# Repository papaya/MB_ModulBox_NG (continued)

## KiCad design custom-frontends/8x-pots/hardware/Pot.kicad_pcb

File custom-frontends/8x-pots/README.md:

# 8x-pots — Module custom 8 potentiomètres rotatifs (AIN)

## Description

Module potentiomètres rotatifs (8 canaux) pour le contrôle de paramètres continus MIDI (volume, filtre, effets, etc.). Chaque potentiomètre est lu sur une voie analogique indépendante. La carte ne contient **aucun convertisseur analogique-numérique** : elle expose 8 curseurs sur un connecteur IDC, reliés au module **AINSER64** (MCP3208 + CD4051) du bus AIN.

## Spécifications techniques

- 8 potentiomètres rotatifs (10 kΩ), empreinte `RK09L and RK09D`
- **Tension de référence : +3V0** (et non +5V) — la borne `+3V0` alimente les deux extrémités de chaque potentiomètre
- Sortie : 8 curseurs + GND + +3V0 sur un connecteur **IDC 2x05 P2.54mm** (`J1`)
- Lecture : via le module **AINSER64** du bus AIN (broche `J19` du Core32F4, SPI)
- Aucune résistance, aucun condensateur, aucun circuit actif sur la carte

## Composants principaux

| Type | Dénomination | Qté |
|------|-------------|-----|
| Potentiomètre rotatif | RK09D1130C1B / RK09L1140A5L (10 kΩ) | 8 |
| Connecteur | IDC Header 2x05 P2.54mm Vertical (`J1`) | 1 |
| Vis de fixation | MountingHole 3.2mm M3 | 6 |

> Il n'y a **pas de LED sur cette carte**
## Brochage / Mapping MIDIbox NG

### Connecteur `J1` — vers module AINSER64 (bus AIN, `J19` du Core)

| Broche | Signal | Description |
|--------|--------|-------------|
| 1 | GND | Masse commune (référence 0 V) |
| 2 | +3V0 | Alimentation des potentiomètres (borne haute) |
| 3 | `J1-A0` | Curseur du potentiomètre **pot2** |
| 4 | `J1-A1` | Curseur du potentiomètre **pot1** |
| 5 | `J1-A2` | Curseur du potentiomètre **pot3** |
| 6 | `J1-A3` | Curseur du potentiomètre **pot6** |
| 7 | `J1-A4` | Curseur du potentiomètre **pot4** |
| 8 | `J1-A5` | Curseur du potentiomètre **pot7** |
| 9 | `J1-A6` | Curseur du potentiomètre **pot5** |
| 10 | `J1-A7` | Curseur du potentiomètre **pot8** |

> **Câblage du potentiomètre (vérifié dans le schéma KiCad)** : patte 1 → GND, patte 2 → **curseur** (→ broche `J1` correspondante), patte 3 → **+3V0**.

> Le curseur étant relié à l'entrée analogique de l'AINSER64, la plage de mesure est **0 .. 3,0 V** (et non 0 .. 5 V). L'AINSER64 (ADC MCP3208 12 bits) mesure donc 0..3 V avec une résolution effective d'environ 10 bits.

> **Les entrées analogiques non utilisées de l'AINSER64 doivent être reliées à la masse**, sinon l'application émet des valeurs aléatoires.

### Module AINSER64 (rappel)

- Connecteur : **`J19`** du Core STM32F4 (SPI, 2 chip-selects `RC1`/`RC2`)
- Architecture : 1 × **MCP3208** (ADC 12 bits) + 8 × **CD4051** (multiplexeurs 8:1) + 1 × 74HC595
- Capacité : 64 entrées par module, jusqu'à 2 modules (128 voies) supportés par MIDIbox NG
- Les 8 entrées de chaque connecteur `J6`..`J13` de l'AINSER64 disposent de **+5V et GND** dédiés ; si la tension de référence de 3,0 V est souhaitée, alimenter les potentiomètres séparément (c'est le cas ici : +3V0 local à la carte)

## Variante `Pot-X2` (montage 4x2)

- `hardware/Pot-X2.kicad_pcb` : variante **2 plaques de 4 potentiomètres** empilées (41 empreintes)
- ⚠️ **Cette variante n'a pas de schéma KiCad associé** et contient des empreintes non annotées (`REF**`) ainsi que 10 pads non connectés : elle est fournie **pour référence**, à vérifier avant fabrication
- Le schéma `Pot.kicad_sch` correspond à la variante **verticale** (8 potentiomètres sur une plaque)

## Notes de montage et astuces DIY

- Vérifier le câblage du curseur vers la broche `J1` avant mise sous tension
- Les potentiomètres sont sur la carte verticale ; l'empilement 4x2 (`Pot-X2`) est mécaniquement séparé
- Fichiers 3D : Potars_V4.wrl (boîtier), Potars_eurorack.step (montage Eurorack)

## Documentation de fabrication

- `hardware/` : sources KiCad (`Pot.kicad_pro`, `Pot.kicad_sch`, `Pot.kicad_pcb`, + variante `Pot-X2.kicad_pcb`)
- `hardware/3D/` : modèles 3D des potentiomètres (`.wrl`, `.step`)
- `production/` : Gerbers, BOM (Pot.csv), netlist (`.xml`), archives de fabrication
- Blog : [4X2-POTS-v0.2 sur ksir-diy.blogspot.com](https://ksir-diy.blogspot.com/)
## Assets de visualisation

| Type | Fichier | Description |
|------|---------|-------------|
| Top view | `3d-top.png` | Vue de dessus du PCB |
| Iso 3D | `3d-iso.png` | Vue isométrique avec composants |
| Pot 4x2 | `pot4x2.png` | Vue du montage 4x2 pots |
| Screenshot | `Screenshot%202023-05-19%20153745.png` | Capture d'écran du design |

---

## Conception & Compatibilité

Carte d'interface **originale MB MODULBOX NG** (conception Ksir), compatible avec les bus et modules du système MIDIbox NG. Ce n'est **pas** un module officiel MIDIbox.

> **Origine et usage :** conception originale MB MODULBOX NG, prévue pour le DIY/personnel. Aucune licence formelle n'est publiée dans le dépôt ; voir le README racine. **Aucune garantie ni engagement** n'est fourni sur la justesse du câblage ou du routage.

> ⚠️ **Avertissement :** documentation de passion, **non professionnelle**. Fournie **sans garantie ni engagement**, **sans support technique**. Des **erreurs sont possibles** (schémas, valeurs, câblage). À vos risques et périls : vérifiez tout avant de fabriquer et de mettre sous tension.

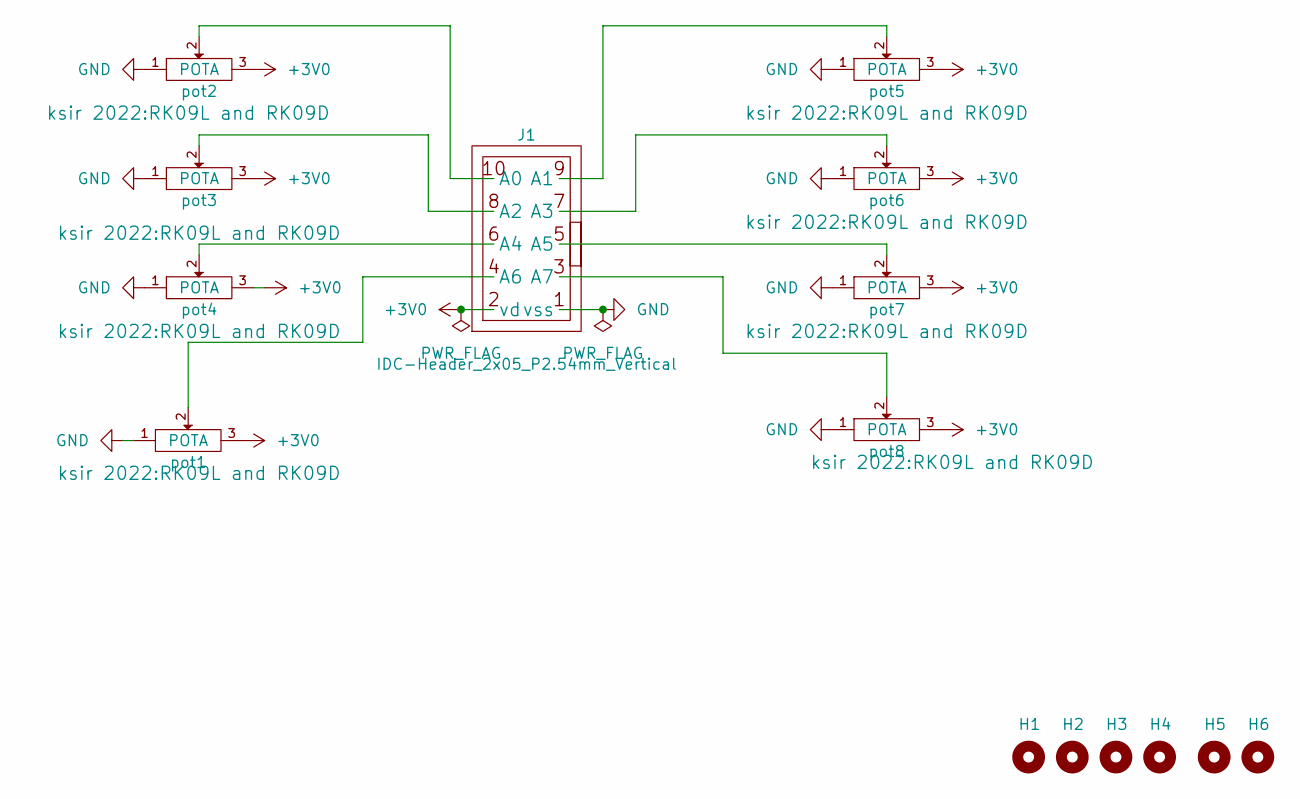
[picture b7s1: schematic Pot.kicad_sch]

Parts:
H1, H2, H3, H4, H5, H6: MountingHole; MountingHole_3.2mm_M3
J1: IDC-Header_2x05_P2.54mm_Vertical
pot1, pot2, pot3, pot4, pot5, pot6, pot7, pot8: POTA; RK09L and RK09D

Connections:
+3V0: J1.2 (vd), pot1.3 (vd), pot2.3 (vd), pot3.3 (vd), pot4.3 (vd), pot5.3 (vd), pot6.3 (vd), pot7.3 (vd), pot8.3 (vd)
GND: J1.1 (vss), pot1.1 (vss_masse), pot2.1 (vss_masse), pot3.1 (vss_masse), pot4.1 (vss_masse), pot5.1 (vss_masse), pot6.1 (vss_masse), pot7.1 (vss_masse), pot8.1 (vss_masse)
unnamed: J1.10 (A0), pot2.2
unnamed: J1.9 (A1), pot5.2
unnamed: J1.8 (A2), pot3.2
unnamed: J1.7 (A3), pot6.2
unnamed: J1.6 (A4), pot4.2
unnamed: J1.5 (A5), pot7.2
unnamed: J1.4 (A6), pot1.2
unnamed: J1.3 (A7), pot8.2

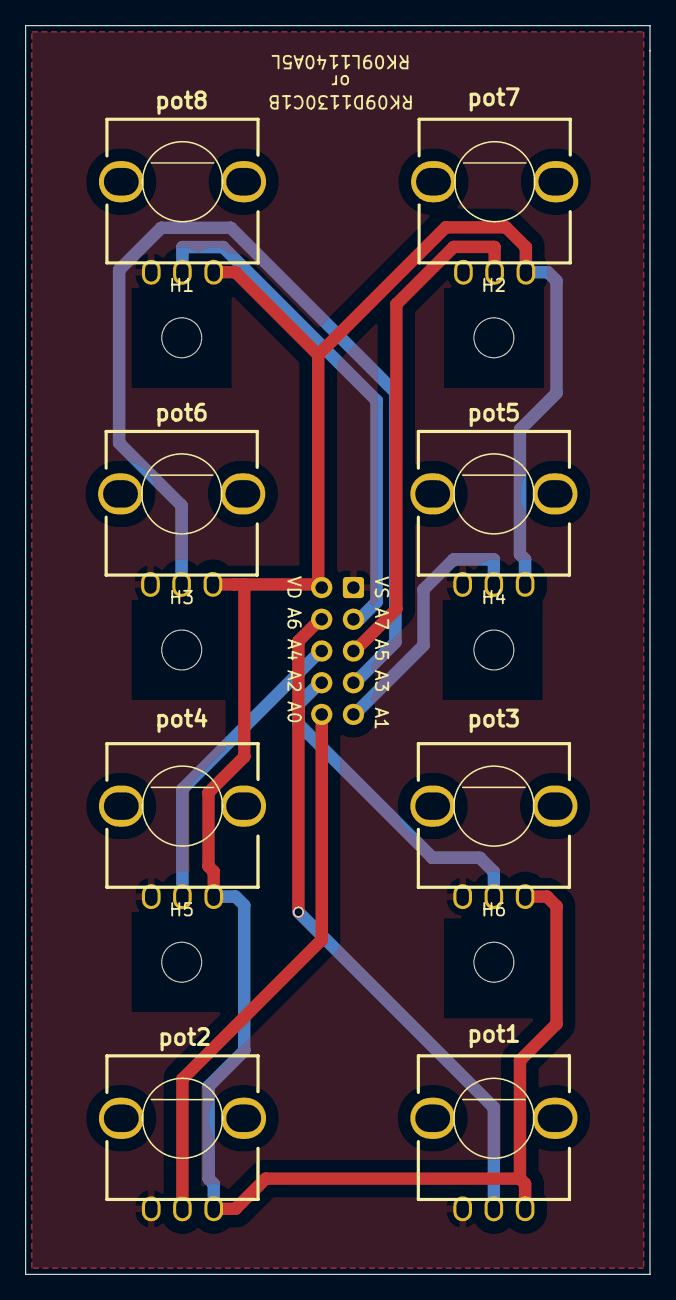
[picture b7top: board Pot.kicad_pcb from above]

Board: 2 copper layers, 50.0 x 100.0 mm, 15 parts (1 on the bottom side), 10 nets.

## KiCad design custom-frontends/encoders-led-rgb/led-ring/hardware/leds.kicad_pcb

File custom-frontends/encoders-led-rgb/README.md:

# encoders-led-rgb — Carte 8 encodeurs PEC16 + 128 LED WS2812 (DIN + WS2812)

## Description
Carte de front-end integrant **8 encodeurs rotatifs avec poussoir** (PEC16) et **128 LED RGB adressables WS2812** (anneaux lumineux). Chaque encodeur genere des evenements MIDI via le **bus DIN**, et l'eclairage est commande par **une ligne de donnees WS2812**, les 128 LED etant **cascadees en serie**.
Se compose de 3 PCB;
un pcb avec les leds
un pcb avec les encodeurs
un pcb pour les connecteurs
un front panel en aluminium 
des diffuseur de lumiere translucide imprimé en 3d
des masque de lumiere imprimé en 3d noir pour empecher la lumiére de se diffuser ailleur  
📖 **Article de référence :** [4X2 ENC-SW-16-LED-RING-RGB (PEC16)](https://ksir-diy.blogspot.com/) sur le blog Ksir DIY'S — modèles PEC16 fonctionne, déja testé!

> ⚠️ Attention a la consomation des leds , j'ai baissé la luminosité a entre 5 et 10 % pour garder une consomation limité (entre 0,5 et 1 A sur la consomation totale du controleur)
> ⚠️ **Les LED WS2812 ne se connectent PAS sur le bus DOUT (74HC595).** Elles recoivent une ligne de donnees specifique d'une sortie WS2812 du **Core32F4** (`J4A` / `J4B`). L'alimentation 5V des LED doit etre fournie **separement** (pas via `J4A`/`J4B`).
>
> **Les 128 LED WS2812 sont en cascade** au niveau du cablage physique (chaine de donnees),  **elles sont adressables individuellement**. Il est possible de commander chaque LED a une couleur differente.

## Spécifications techniques
- **8 encodeurs rotatifs avec poussoir integre** — PEC16 (`PEC16-4XXXF-SXXXX`, empreinte `PEC164120FS0012`) : 2 sorties de phase (A, B) + 1 poussoir
- **24 entrees DIN** au total (8 × A, 8 × B, 8 × poussoir), reparties sur 3 connecteurs `J11`, `J12`, `J13`
- **128 × WS2812-2020** (PLCC4 2.0 × 2.0 mm) en **cascade serie** unique : `J4` -> D1 -> D2 -> ... -> D128 -> `J5`
- 128 × condensateur de decoupling 100 nF sur chaque LED
- **Aucune resistance de pull-up sur la carte** : le pull-up 10 kΩ est porte par le module **DIN** (74HC165)
- 2 alimentations distinctes : `+5VA` (analogique, `J44`) et `+5VD` (digitale, `J45`)

## Composants principaux
| Type | Dénomination | Qté |
|------|-------------|-----|
| Encodeur rotatif a poussoir | PEC16 (`PEC164120FS0012`) | 8 |
| LED RGB adressable | WS2812B (`LED_WS2812B-2020_PLCC4_2.0x2.0mm`) | 128 |
| Condensateur | C 100 nF | 128 |
| Connecteur DIN | IDC Header 2x05 (`J11`, `J12`, `J13`) | 3 |
| Connecteur WS2812 | PinSocket 1x03 (`J4` entree, `J5` sortie) | 2 |
| Connecteur alimentation | IDC 2x05 (`J44` = +5VA, `J45` = +5VD) | 2 |
| Connecteurs de report | PinHeader / PinSocket 1x03 et 1x06 (`J14`, `J15`, `J20`-`J25`, `J30`-`J35`) | 18 |

## Brochage / Mapping MIDIbox NG

### `J11` — poussoirs des encodeurs (8 entrees DIN) Se connecte sur carte DIN 
| Broche | Signal | Description |
|--------|--------|-------------|
| 1 | GND | Masse commune |
| 2 | — | Non connectee |
| 3 | `C_SW8` | Poussoir de l'encodeur **8** |
| 4 | `C_SW7` | Poussoir de l'encodeur **7** |
| 5 | `C_SW6` | Poussoir de l'encodeur **6** |
| 6 | `C_SW5` | Poussoir de l'encodeur **5** |
| 7 | `C_SW4` | Poussoir de l'encodeur **4** |
| 8 | `C_SW3` | Poussoir de l'encodeur **3** |
| 9 | `C_SW2` | Poussoir de l'encodeur **2** |
| 10 | `C_SW1` | Poussoir de l'encodeur **1** |

### `J12` — phases B/A des encodeurs 5 a 8 Se connecte sur carte DIN 
| Broche | Signal | Description |
|--------|--------|-------------|
| 1 | GND | Masse commune |
| 2 | — | Non connectee |
| 3 | `C_ENC8B` | Phase B encodeur **8** |
| 4 | `C_ENC8A` | Phase A encodeur **8** |
| 5 | `C_ENC7B` | Phase B encodeur **7** |
| 6 | `C_ENC7A` | Phase A encodeur **7** |
| 7 | `C_ENC6B` | Phase B encodeur **6** |
| 8 | `C_ENC6A` | Phase A encodeur **6** |
| 9 | `C_ENC5B` | Phase B encodeur **5** |
| 10 | `C_ENC5A` | Phase A encodeur **5** |

### `J13` — phases B/A des encodeurs 1 a 4 Se connecte sur carte DIN 
| Broche | Signal | Description |
|--------|--------|-------------|
| 1 | GND | Masse commune |
| 2 | — | Non connectee |
| 3 | `C_ENC4B` | Phase B encodeur **4** |
| 4 | `C_ENC4A` | Phase A encodeur **4** |
| 5 | `C_ENC3B` | Phase B encodeur **3** |
| 6 | `C_ENC3A` | Phase A encodeur **3** |
| 7 | `C_ENC2B` | Phase B encodeur **2** |
| 8 | `C_ENC2A` | Phase A encodeur **2** |
| 9 | `C_ENC1B` | Phase B encodeur **1** |
| 10 | `C_ENC1A` | Phase A encodeur **1** |

> Les encodeurs sont raccordes aux connecteurs de report `J30`..`J35` (1x06), qui reprennent les memes signaux `C_SWx`, `C_ENCxA`, `C_ENCxB` pour le routage physique vers les encodeurs.
>
> Les phases A/B constituent les **entrees d'un compteur de quadrature** : elles sont branchees sur deux entrees consecutives d'un registre **74HC165** du module DIN. Les poussoirs, eux, sont des contacts **vers GND**.

### `J4` / `J5` — cascade WS2812 J4 Se connecte sur j4b du core32f4 ou sur J5 du module precedent
| Connecteur | Broche | Signal | Description |
|------------|--------|--------|-------------|
| `J4` | 1 | +5V | Alimentation des LED |
| `J4` | 2 | `D1-DI` | **DATA d'entree** de la cascade (vers `D1`) |
| `J4` | 3 | GND | Masse |
| `J5` | 1 | +5V | Alimentation des LED |
| `J5` | 2 | `D128-DO` | **DATA de sortie** de la cascade (depuis `D128`) |
| `J5` | 3 | GND | Masse |

```
Core (J4A/J4B, WS2812)  ->  J4 (broche 2)  ->  D1 -> D2 -> ... -> D128  ->  J5 (broche 2)
```

### `J44` / `J45` — alimentations
| Connecteur | Broche | Signal | Description |
|------------|--------|--------|-------------|
| `J44` | 1 | GND | Masse analogique (`GNDA`) |
| `J44` | 6 | `J34-Pin_2` | Report vers `J34` |
| `J44` | 10 | +5VA | Alimentation **analogique** |
| `J45` | 1 | GND | Masse analogique (`GNDA`) |
| `J45` | 6 | `J35-Pin_2` | Report vers `J35` |
| `J45` | 10 | +5VD | Alimentation **digitale** |

### Chaine WS2812 du Core
- Le Core STM32F4 dispose de **4 lignes WS2812** (`J4A` PB10 / PB11, `J4B` **PB6** = TIM4 (reference MIOS32) / `J4B` PB9), chacune avec un pull-up 2,2 kΩ et une sortie en open-drain.
- **L'alimentation +5V des LED doit etre fournie separement** (jusqu'a 20 mA par LED RGB, soit 2,5 A pour 128 LED a pleine luminosite). Voir [specifications WS2812 MIOS32](https://www.midibox.org/mios32/midibox_ng/group___w_s2812.html).
- Avec 128 LED en cascade sur une seule ligne, la longueur de piste et le nombre de LED restent dans les limites du protocole WS2812, mais **le routage de la carte presente 315 violations DRC** : a verifier avant fabrication.

## Documentation de fabrication
- `hardware/` : schéma historique global et PCB restauré (`PEC_16_V0.2.*`)
- `control-board/`, `encoders-board/`, `led-ring/` : PCB distincts, chacun documenté dans son dossier
- `production/` : BOM, positions et netlist uniquement ; aucun Gerber de sous-carte n'est versionné
- `mechanical/` : emplacement documentaire des sources de façade, absentes de l'inventaire local
- `libs/` : symboles et empreintes spécifiques si non partagés

### État de la séparation en trois cartes

Les PCB de la Control Board, de l'Encoders Board et du LED Ring existent déjà dans trois sous-dossiers. En revanche, les sous-projets ne sont pas encore autonomes : aucun ne dispose d'un schéma indépendant vérifié, les exports de fabrication ne sont pas séparés par PCB, et des configurations KiCad orphelines subsistent. Le schéma `hardware/PEC_16_V0.2.kicad_sch` reste la référence historique de l'ensemble ; il n'a pas été dupliqué artificiellement en trois schémas qui ne correspondraient pas aux cartes.

Les modèles STEP/WRL locaux ne sont pas versionnés et certaines références de modèles dans les PCB sont des chemins absolus Windows. Voir [`docs/interconnect.md`](docs/interconnect.md) et [`mechanical/README.md`](mechanical/README.md) avant de s'appuyer sur les rendus 3D ou l'assemblage.

---

## Conception & Compatibilité

Carte d'interface **originale MB MODULBOX NG** (conception Ksir), compatible avec les bus et modules du système MIDIbox NG. Ce n'est **pas** un module officiel MIDIbox.

> **Origine et usage :** conception originale MB MODULBOX NG, prévue pour le DIY/personnel. Aucune licence formelle n'est publiée dans le dépôt ; voir le README racine. **Aucune garantie ni engagement** n'est fourni sur la justesse du câblage ou du routage.

🔋 **Gestion de la puissance** : La gestion de la puissance des LED est indispensable, j'ai paramétré les LED à 10% de puissance.
Conception originale MB MODULBOX NG. > ⚠️ **Avertissement :** documentation de passion, **non professionnelle**. Fournie **sans garantie ni engagement**, **sans support technique**. Des **erreurs sont possibles** (schémas, valeurs, câblage). À vos risques et périls : vérifiez tout avant de fabriquer et de mettre sous tension.

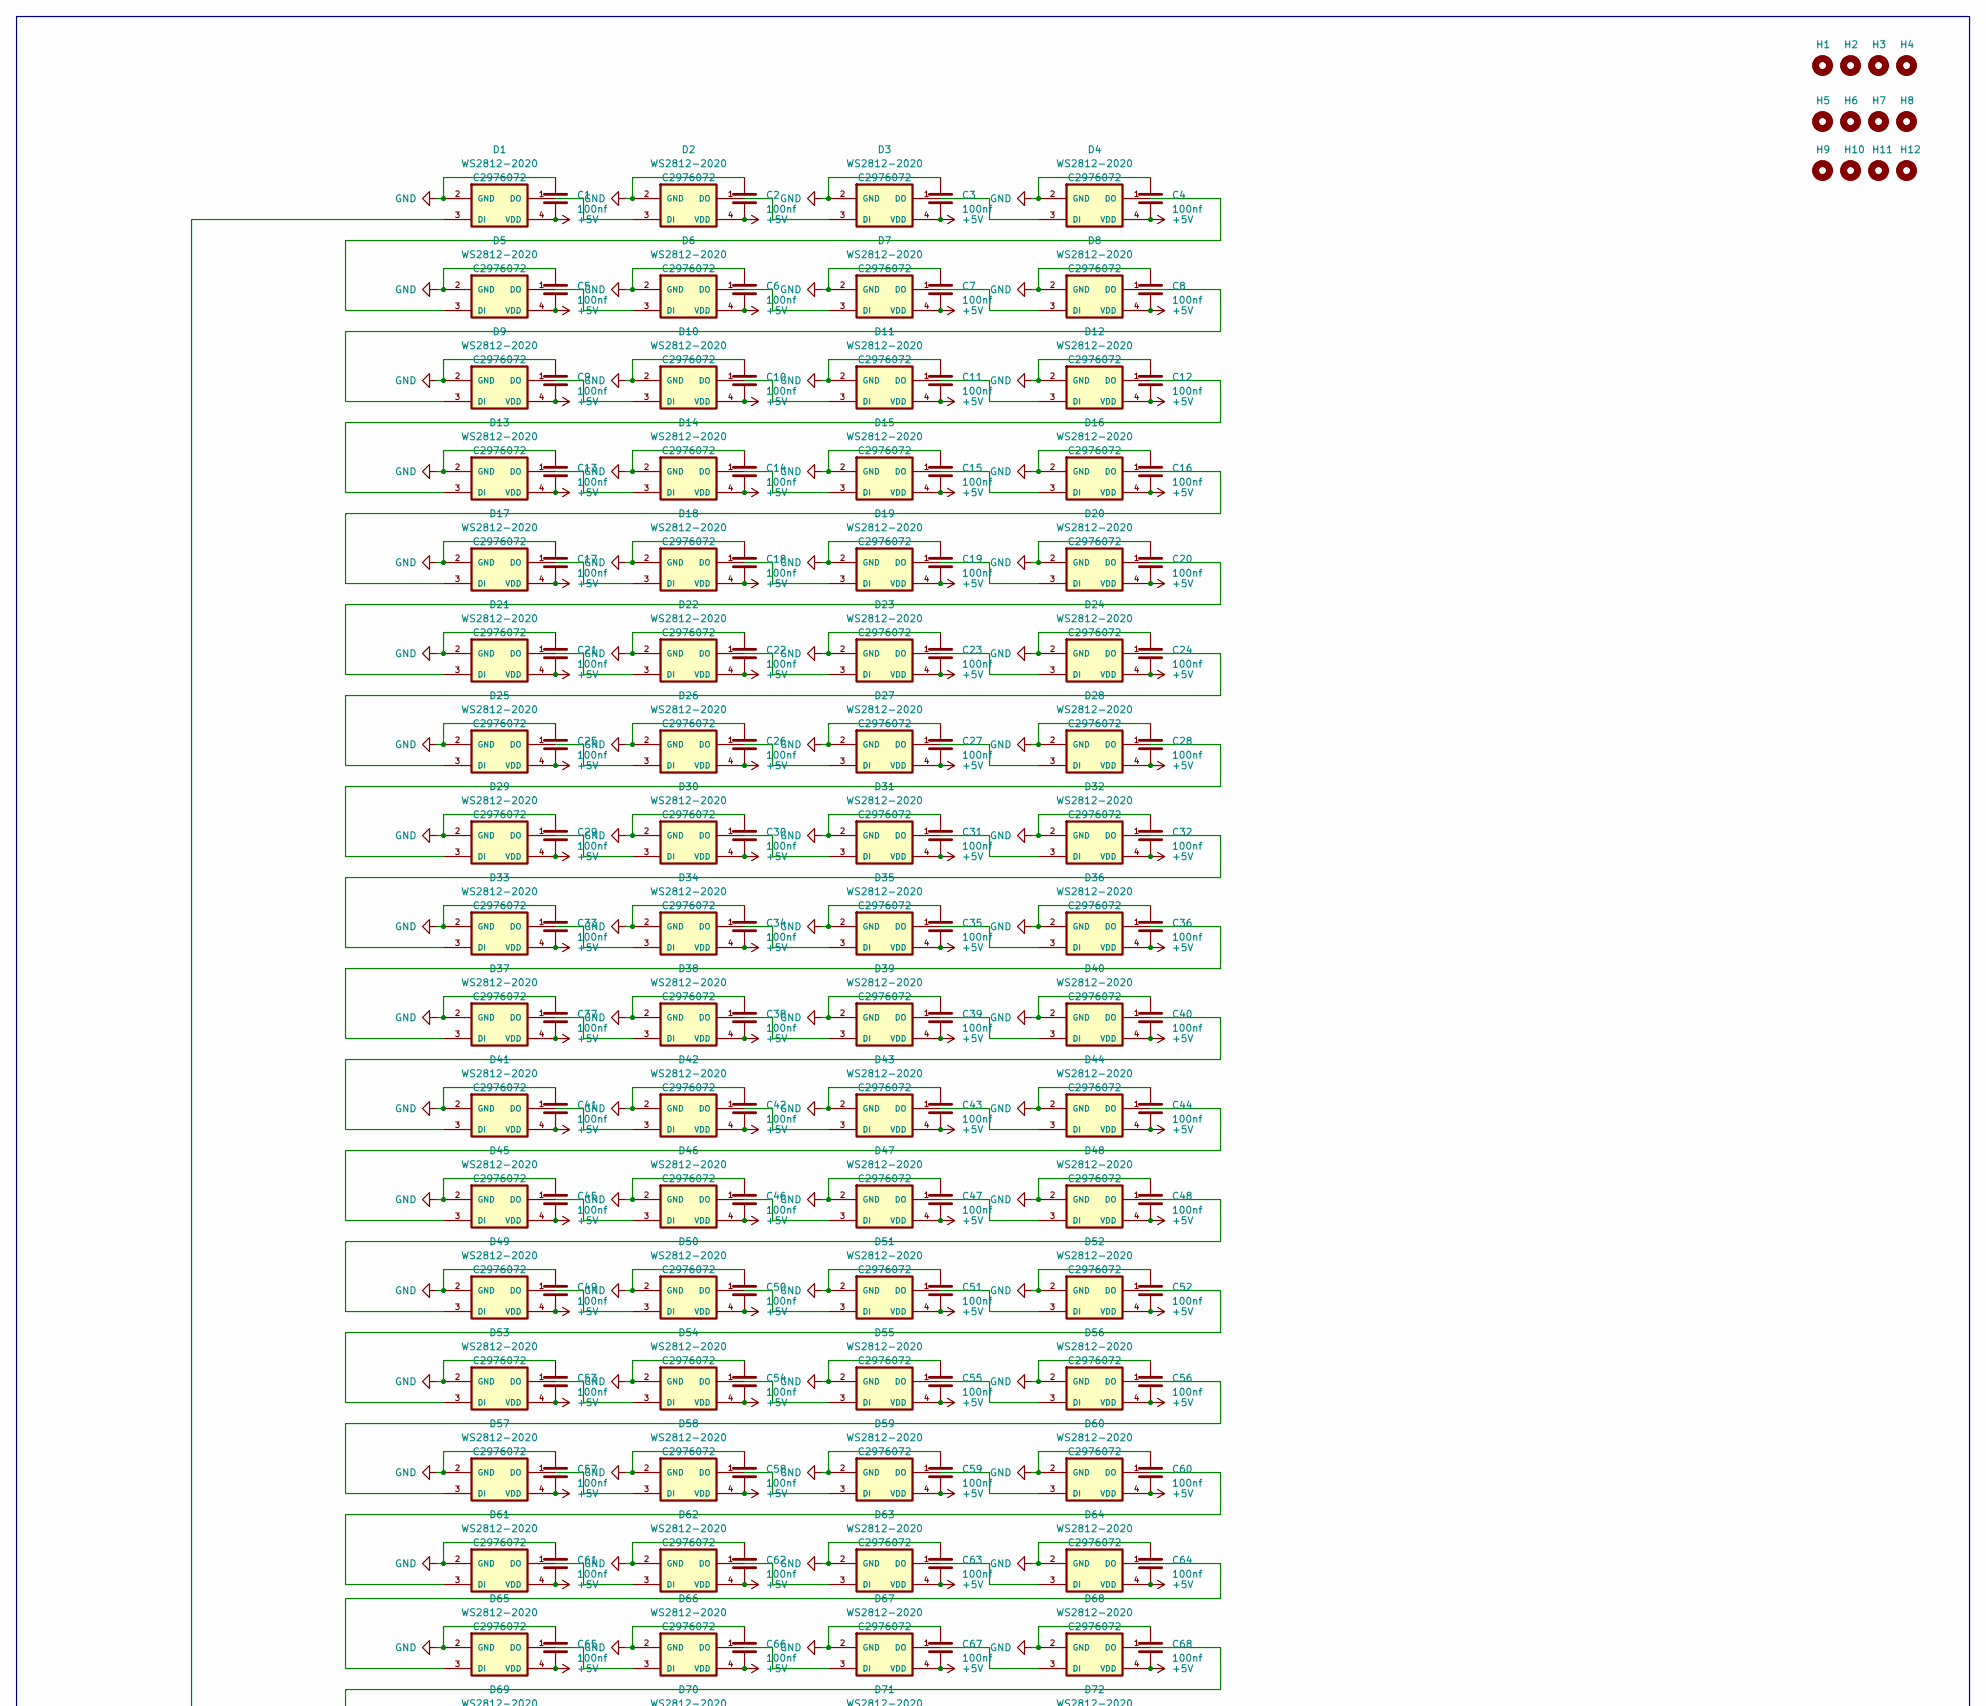
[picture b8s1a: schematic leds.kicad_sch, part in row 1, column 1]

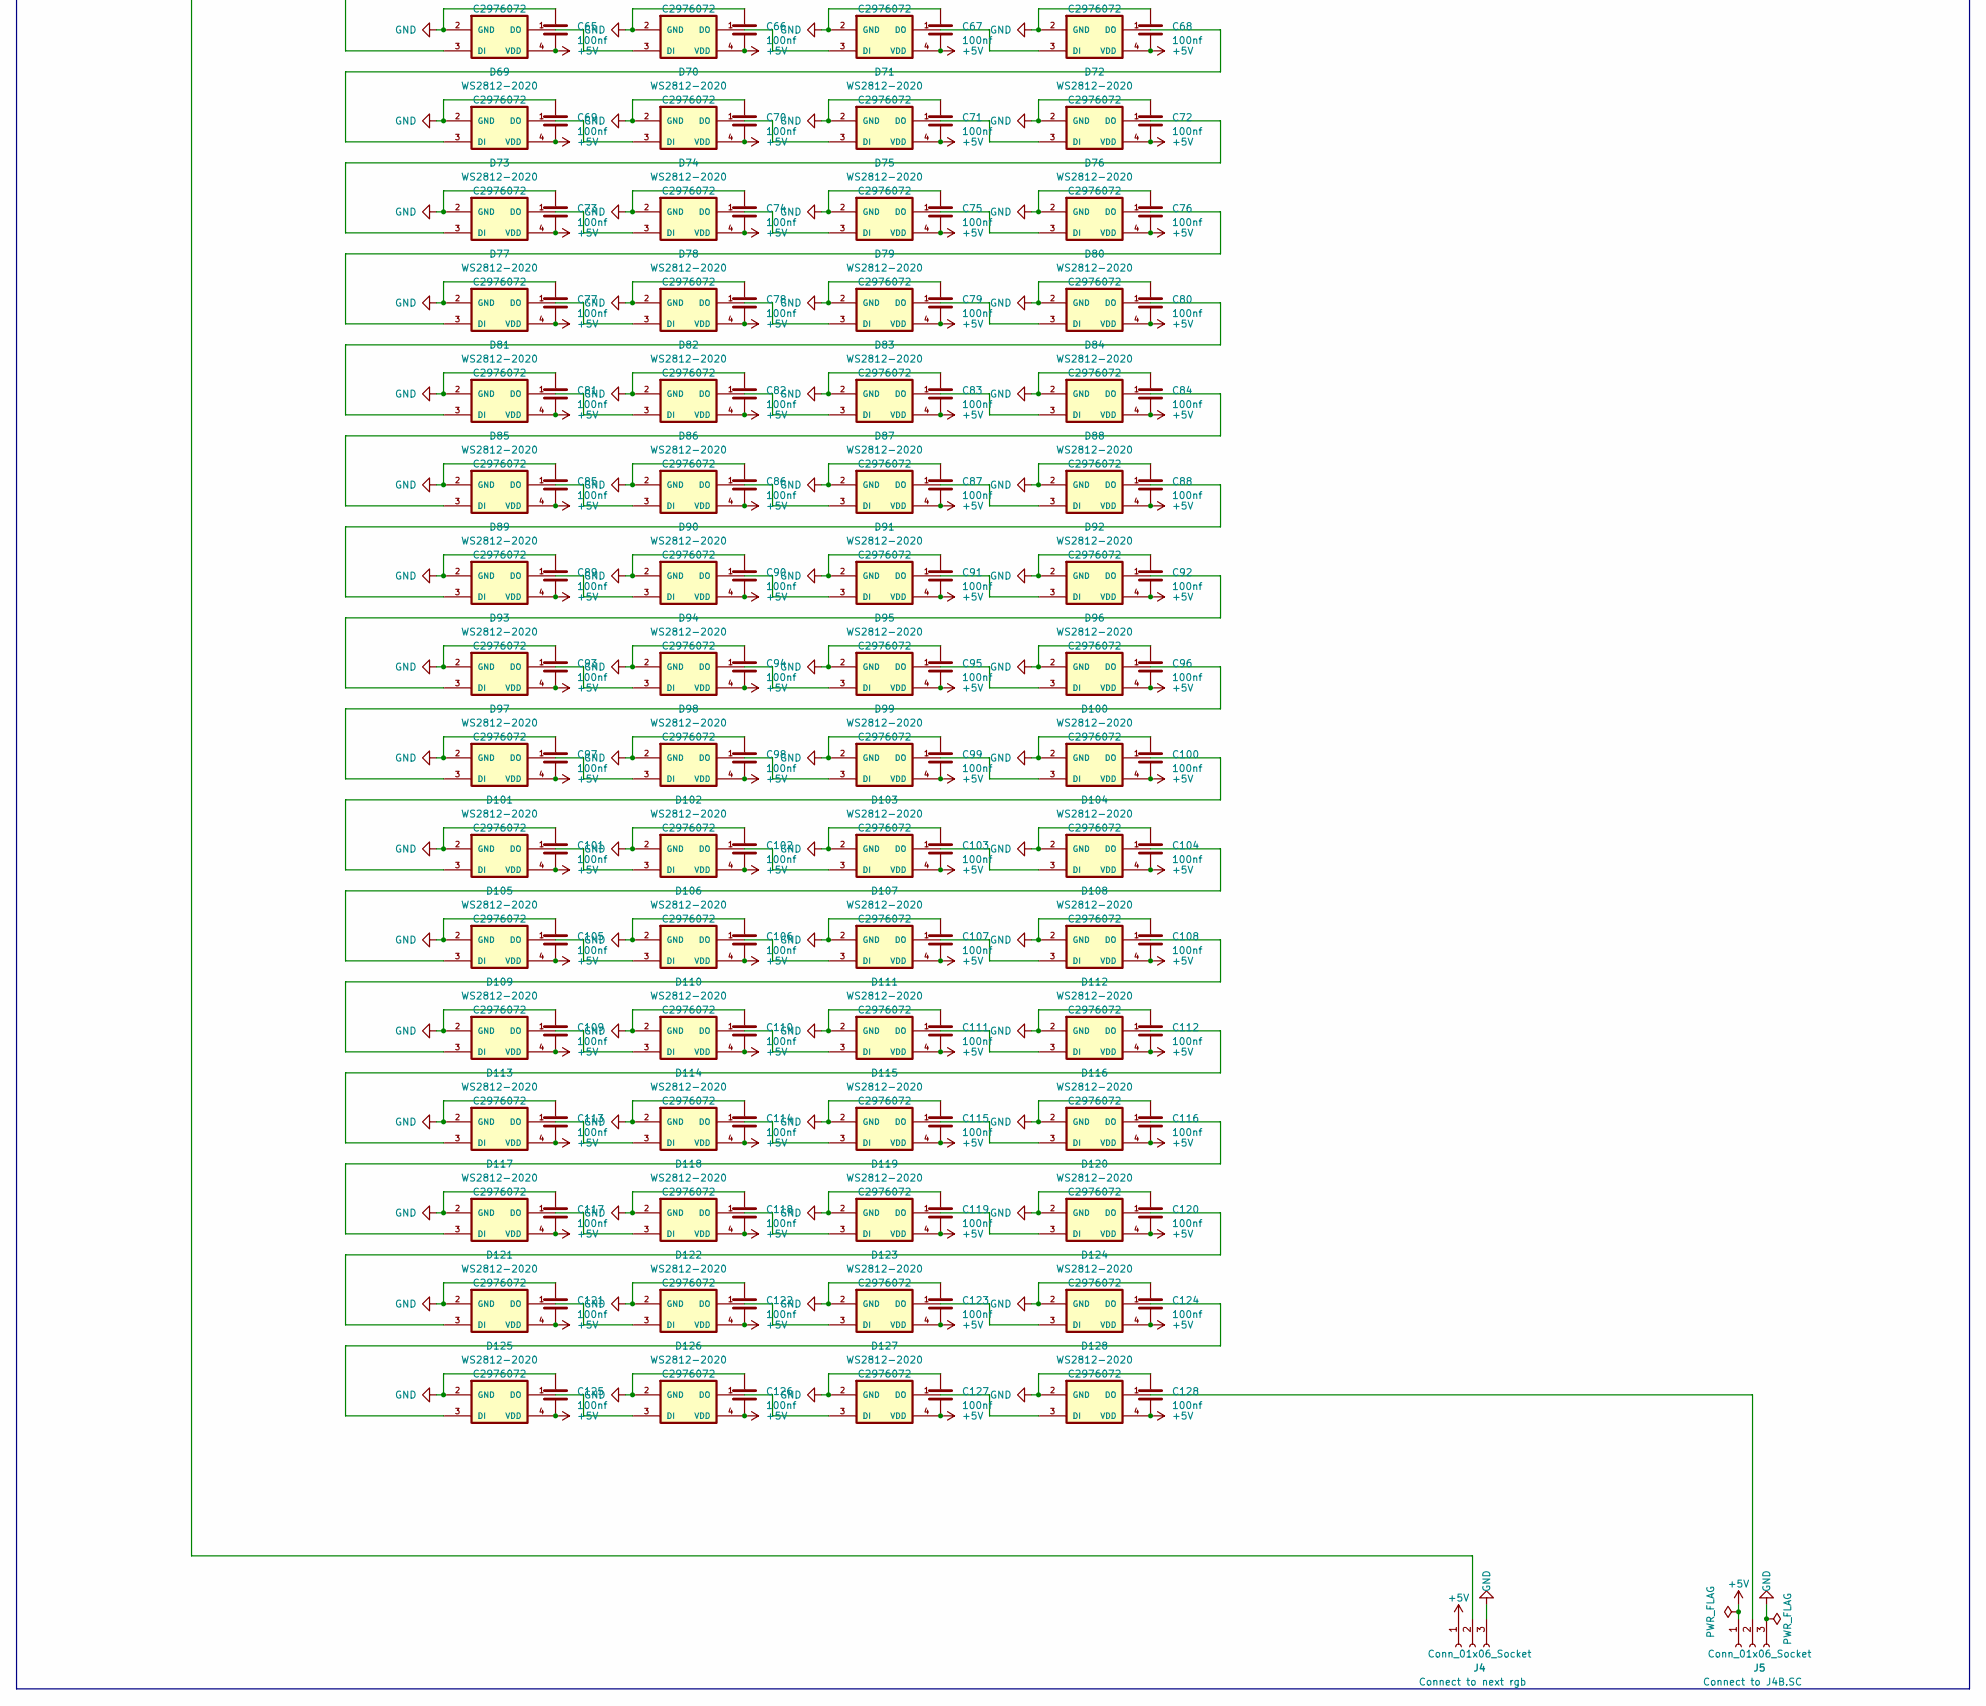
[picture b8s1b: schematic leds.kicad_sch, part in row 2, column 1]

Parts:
C1, C2, C3, C4, C5, C6, C7, C8, C9, C10, C11, C12, C13, C14, C15, C16, C17, C18, C19, C20, C21, C22, C23, C24, C25, C26, C27, C28, C29, C30, C31, C32, C33, C34, C35, C36, C37, C38, C39, C40, C41, C42, C43, C44, C45, C46, C47, C48, C49, C50, C51, C52, C53, C54, C55, C56, C57, C58, C59, C60, C61, C62, C63, C64, C65, C66, C67, C68, C69, C70, C71, C72, C73, C74, C75, C76, C77, C78, C79, C80, C81, C82, C83, C84, C85, C86, C87, C88, C89, C90, C91, C92, C93, C94, C95, C96, C97, C98, C99, C100, C101, C102, C103, C104, C105, C106, C107, C108, C109, C110, C111, C112, C113, C114, C115, C116, C117, C118, C119, C120, C121, C122, C123, C124, C125, C126, C127, C128: 100nf; CAPC1005X55N; JLCPCB Part # C1525
D1, D2, D3, D4, D5, D6, D7, D8, D9, D10, D11, D12, D13, D14, D15, D16, D17, D18, D19, D20, D21, D22, D23, D24, D25, D26, D27, D28, D29, D30, D31, D32, D33, D34, D35, D36, D37, D38, D39, D40, D41, D42, D43, D44, D45, D46, D47, D48, D49, D50, D51, D52, D53, D54, D55, D56, D57, D58, D59, D60, D61, D62, D63, D64, D65, D66, D67, D68, D69, D70, D71, D72, D73, D74, D75, D76, D77, D78, D79, D80, D81, D82, D83, D84, D85, D86, D87, D88, D89, D90, D91, D92, D93, D94, D95, D96, D97, D98, D99, D100, D101, D102, D103, D104, D105, D106, D107, D108, D109, D110, D111, D112, D113, D114, D115, D116, D117, D118, D119, D120, D121, D122, D123, D124, D125, D126, D127, D128: WS2812-2020; LED_WS2812B-2020_PLCC4_2.0x2.0mm; JLCPCB Part # C2976072
H1, H2, H3, H4: MountingHole; MountingHole_3.2mm_M3
H5, H6, H7, H8, H9, H10, H11, H12: MountingHole; Hole_9.5mm
J4, J5: Conn_01x06_Socket; PinSocket_1x03_P2.54mm_Vertical

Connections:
+5V: C1.2, C2.2, C3.2, C4.2, C5.2, C6.2, C7.2, C8.2, C9.2, C10.2, C11.2, C12.2, C13.2, C14.2, C15.2, C16.2, C17.2, C18.2, C19.2, C20.2, C21.2, C22.2, C23.2, C24.2, C25.2, C26.2, C27.2, C28.2, C29.2, C30.2, C31.2, C32.2, C33.2, C34.2, C35.2, C36.2, C37.2, C38.2, C39.2, C40.2, C41.2, C42.2, C43.2, C44.2, C45.2, C46.2, C47.2, C48.2, C49.2, C50.2, C51.2, C52.2, C53.2, C54.2, C55.2, C56.2, C57.2, C58.2, C59.2, C60.2, C61.2, C62.2, C63.2, C64.2, C65.2, C66.2, C67.2, C68.2, C69.2, C70.2, C71.2, C72.2, C73.2, C74.2, C75.2, C76.2, C77.2, C78.2, C79.2, C80.2, C81.2, C82.2, C83.2, C84.2, C85.2, C86.2, C87.2, C88.2, C89.2, C90.2, C91.2, C92.2, C93.2, C94.2, C95.2, C96.2, C97.2, C98.2, C99.2, C100.2, C101.2, C102.2, C103.2, C104.2, C105.2, C106.2, C107.2, C108.2, C109.2, C110.2, C111.2, C112.2, C113.2, C114.2, C115.2, C116.2, C117.2, C118.2, C119.2, C120.2, C121.2, C122.2, C123.2, C124.2, C125.2, C126.2, C127.2, C128.2, D1.4 (VDD), D2.4 (VDD), D3.4 (VDD), D4.4 (VDD), D5.4 (VDD), D6.4 (VDD), D7.4 (VDD), D8.4 (VDD), D9.4 (VDD), D10.4 (VDD), D11.4 (VDD), D12.4 (VDD), D13.4 (VDD), D14.4 (VDD), D15.4 (VDD), D16.4 (VDD), D17.4 (VDD), D18.4 (VDD), D19.4 (VDD), D20.4 (VDD), D21.4 (VDD), D22.4 (VDD), D23.4 (VDD), D24.4 (VDD), D25.4 (VDD), D26.4 (VDD), D27.4 (VDD), D28.4 (VDD), D29.4 (VDD), D30.4 (VDD), D31.4 (VDD), D32.4 (VDD), D33.4 (VDD), D34.4 (VDD), D35.4 (VDD), D36.4 (VDD), D37.4 (VDD), D38.4 (VDD), D39.4 (VDD), D40.4 (VDD), D41.4 (VDD), D42.4 (VDD), D43.4 (VDD), D44.4 (VDD), D45.4 (VDD), D46.4 (VDD), D47.4 (VDD), D48.4 (VDD), D49.4 (VDD), D50.4 (VDD), D51.4 (VDD), D52.4 (VDD), D53.4 (VDD), D54.4 (VDD), D55.4 (VDD), D56.4 (VDD), D57.4 (VDD), D58.4 (VDD), D59.4 (VDD), D60.4 (VDD), D61.4 (VDD), D62.4 (VDD), D63.4 (VDD), D64.4 (VDD), D65.4 (VDD), D66.4 (VDD), D67.4 (VDD), D68.4 (VDD), D69.4 (VDD), D70.4 (VDD), D71.4 (VDD), D72.4 (VDD), D73.4 (VDD), D74.4 (VDD), D75.4 (VDD), D76.4 (VDD), D77.4 (VDD), D78.4 (VDD), D79.4 (VDD), D80.4 (VDD), D81.4 (VDD), D82.4 (VDD), D83.4 (VDD), D84.4 (VDD), D85.4 (VDD), D86.4 (VDD), D87.4 (VDD), D88.4 (VDD), D89.4 (VDD), D90.4 (VDD), D91.4 (VDD), D92.4 (VDD), D93.4 (VDD), D94.4 (VDD), D95.4 (VDD), D96.4 (VDD), D97.4 (VDD), D98.4 (VDD), D99.4 (VDD), D100.4 (VDD), D101.4 (VDD), D102.4 (VDD), D103.4 (VDD), D104.4 (VDD), D105.4 (VDD), D106.4 (VDD), D107.4 (VDD), D108.4 (VDD), D109.4 (VDD), D110.4 (VDD), D111.4 (VDD), D112.4 (VDD), D113.4 (VDD), D114.4 (VDD), D115.4 (VDD), D116.4 (VDD), D117.4 (VDD), D118.4 (VDD), D119.4 (VDD), D120.4 (VDD), D121.4 (VDD), D122.4 (VDD), D123.4 (VDD), D124.4 (VDD), D125.4 (VDD), D126.4 (VDD), D127.4 (VDD), D128.4 (VDD), J4.1, J5.1
GND: C1.1, C2.1, C3.1, C4.1, C5.1, C6.1, C7.1, C8.1, C9.1, C10.1, C11.1, C12.1, C13.1, C14.1, C15.1, C16.1, C17.1, C18.1, C19.1, C20.1, C21.1, C22.1, C23.1, C24.1, C25.1, C26.1, C27.1, C28.1, C29.1, C30.1, C31.1, C32.1, C33.1, C34.1, C35.1, C36.1, C37.1, C38.1, C39.1, C40.1, C41.1, C42.1, C43.1, C44.1, C45.1, C46.1, C47.1, C48.1, C49.1, C50.1, C51.1, C52.1, C53.1, C54.1, C55.1, C56.1, C57.1, C58.1, C59.1, C60.1, C61.1, C62.1, C63.1, C64.1, C65.1, C66.1, C67.1, C68.1, C69.1, C70.1, C71.1, C72.1, C73.1, C74.1, C75.1, C76.1, C77.1, C78.1, C79.1, C80.1, C81.1, C82.1, C83.1, C84.1, C85.1, C86.1, C87.1, C88.1, C89.1, C90.1, C91.1, C92.1, C93.1, C94.1, C95.1, C96.1, C97.1, C98.1, C99.1, C100.1, C101.1, C102.1, C103.1, C104.1, C105.1, C106.1, C107.1, C108.1, C109.1, C110.1, C111.1, C112.1, C113.1, C114.1, C115.1, C116.1, C117.1, C118.1, C119.1, C120.1, C121.1, C122.1, C123.1, C124.1, C125.1, C126.1, C127.1, C128.1, D1.2 (GND), D2.2 (GND), D3.2 (GND), D4.2 (GND), D5.2 (GND), D6.2 (GND), D7.2 (GND), D8.2 (GND), D9.2 (GND), D10.2 (GND), D11.2 (GND), D12.2 (GND), D13.2 (GND), D14.2 (GND), D15.2 (GND), D16.2 (GND), D17.2 (GND), D18.2 (GND), D19.2 (GND), D20.2 (GND), D21.2 (GND), D22.2 (GND), D23.2 (GND), D24.2 (GND), D25.2 (GND), D26.2 (GND), D27.2 (GND), D28.2 (GND), D29.2 (GND), D30.2 (GND), D31.2 (GND), D32.2 (GND), D33.2 (GND), D34.2 (GND), D35.2 (GND), D36.2 (GND), D37.2 (GND), D38.2 (GND), D39.2 (GND), D40.2 (GND), D41.2 (GND), D42.2 (GND), D43.2 (GND), D44.2 (GND), D45.2 (GND), D46.2 (GND), D47.2 (GND), D48.2 (GND), D49.2 (GND), D50.2 (GND), D51.2 (GND), D52.2 (GND), D53.2 (GND), D54.2 (GND), D55.2 (GND), D56.2 (GND), D57.2 (GND), D58.2 (GND), D59.2 (GND), D60.2 (GND), D61.2 (GND), D62.2 (GND), D63.2 (GND), D64.2 (GND), D65.2 (GND), D66.2 (GND), D67.2 (GND), D68.2 (GND), D69.2 (GND), D70.2 (GND), D71.2 (GND), D72.2 (GND), D73.2 (GND), D74.2 (GND), D75.2 (GND), D76.2 (GND), D77.2 (GND), D78.2 (GND), D79.2 (GND), D80.2 (GND), D81.2 (GND), D82.2 (GND), D83.2 (GND), D84.2 (GND), D85.2 (GND), D86.2 (GND), D87.2 (GND), D88.2 (GND), D89.2 (GND), D90.2 (GND), D91.2 (GND), D92.2 (GND), D93.2 (GND), D94.2 (GND), D95.2 (GND), D96.2 (GND), D97.2 (GND), D98.2 (GND), D99.2 (GND), D100.2 (GND), D101.2 (GND), D102.2 (GND), D103.2 (GND), D104.2 (GND), D105.2 (GND), D106.2 (GND), D107.2 (GND), D108.2 (GND), D109.2 (GND), D110.2 (GND), D111.2 (GND), D112.2 (GND), D113.2 (GND), D114.2 (GND), D115.2 (GND), D116.2 (GND), D117.2 (GND), D118.2 (GND), D119.2 (GND), D120.2 (GND), D121.2 (GND), D122.2 (GND), D123.2 (GND), D124.2 (GND), D125.2 (GND), D126.2 (GND), D127.2 (GND), D128.2 (GND), J4.3, J5.3
unnamed: D1.3 (DI), J4.2
unnamed: D1.1 (DO), D2.3 (DI)
unnamed: D2.1 (DO), D3.3 (DI)
unnamed: D3.1 (DO), D4.3 (DI)
unnamed: D4.1 (DO), D5.3 (DI)
unnamed: D5.1 (DO), D6.3 (DI)
unnamed: D6.1 (DO), D7.3 (DI)
unnamed: D7.1 (DO), D8.3 (DI)
unnamed: D8.1 (DO), D9.3 (DI)
unnamed: D9.1 (DO), D10.3 (DI)
unnamed: D10.1 (DO), D11.3 (DI)
unnamed: D11.1 (DO), D12.3 (DI)
unnamed: D12.1 (DO), D13.3 (DI)
unnamed: D13.1 (DO), D14.3 (DI)
unnamed: D14.1 (DO), D15.3 (DI)
unnamed: D15.1 (DO), D16.3 (DI)
unnamed: D16.1 (DO), D17.3 (DI)
unnamed: D17.1 (DO), D18.3 (DI)
unnamed: D18.1 (DO), D19.3 (DI)
unnamed: D19.1 (DO), D20.3 (DI)
unnamed: D20.1 (DO), D21.3 (DI)
unnamed: D21.1 (DO), D22.3 (DI)
unnamed: D22.1 (DO), D23.3 (DI)
unnamed: D23.1 (DO), D24.3 (DI)
unnamed: D24.1 (DO), D25.3 (DI)
unnamed: D25.1 (DO), D26.3 (DI)
unnamed: D26.1 (DO), D27.3 (DI)
unnamed: D27.1 (DO), D28.3 (DI)
unnamed: D28.1 (DO), D29.3 (DI)
unnamed: D29.1 (DO), D30.3 (DI)
unnamed: D30.1 (DO), D31.3 (DI)
unnamed: D31.1 (DO), D32.3 (DI)
unnamed: D32.1 (DO), D33.3 (DI)
unnamed: D33.1 (DO), D34.3 (DI)
unnamed: D34.1 (DO), D35.3 (DI)
unnamed: D35.1 (DO), D36.3 (DI)
unnamed: D36.1 (DO), D37.3 (DI)
unnamed: D37.1 (DO), D38.3 (DI)
unnamed: D38.1 (DO), D39.3 (DI)
unnamed: D39.1 (DO), D40.3 (DI)
unnamed: D40.1 (DO), D41.3 (DI)
unnamed: D41.1 (DO), D42.3 (DI)
unnamed: D42.1 (DO), D43.3 (DI)
unnamed: D43.1 (DO), D44.3 (DI)
unnamed: D44.1 (DO), D45.3 (DI)
unnamed: D45.1 (DO), D46.3 (DI)
unnamed: D46.1 (DO), D47.3 (DI)
unnamed: D47.1 (DO), D48.3 (DI)
unnamed: D48.1 (DO), D49.3 (DI)
unnamed: D49.1 (DO), D50.3 (DI)
unnamed: D50.1 (DO), D51.3 (DI)
unnamed: D51.1 (DO), D52.3 (DI)
unnamed: D52.1 (DO), D53.3 (DI)
unnamed: D53.1 (DO), D54.3 (DI)
unnamed: D54.1 (DO), D55.3 (DI)
unnamed: D55.1 (DO), D56.3 (DI)
unnamed: D56.1 (DO), D57.3 (DI)
unnamed: D57.1 (DO), D58.3 (DI)
unnamed: D58.1 (DO), D59.3 (DI)
unnamed: D59.1 (DO), D60.3 (DI)
unnamed: D60.1 (DO), D61.3 (DI)
unnamed: D61.1 (DO), D62.3 (DI)
unnamed: D62.1 (DO), D63.3 (DI)
unnamed: D63.1 (DO), D64.3 (DI)
unnamed: D64.1 (DO), D65.3 (DI)
unnamed: D65.1 (DO), D66.3 (DI)
unnamed: D66.1 (DO), D67.3 (DI)
unnamed: D67.1 (DO), D68.3 (DI)
unnamed: D68.1 (DO), D69.3 (DI)
unnamed: D69.1 (DO), D70.3 (DI)
unnamed: D70.1 (DO), D71.3 (DI)
unnamed: D71.1 (DO), D72.3 (DI)
unnamed: D72.1 (DO), D73.3 (DI)
unnamed: D73.1 (DO), D74.3 (DI)
unnamed: D74.1 (DO), D75.3 (DI)
unnamed: D75.1 (DO), D76.3 (DI)
unnamed: D76.1 (DO), D77.3 (DI)
unnamed: D77.1 (DO), D78.3 (DI)
unnamed: D78.1 (DO), D79.3 (DI)
unnamed: D79.1 (DO), D80.3 (DI)
unnamed: D80.1 (DO), D81.3 (DI)
unnamed: D81.1 (DO), D82.3 (DI)
unnamed: D82.1 (DO), D83.3 (DI)
unnamed: D83.1 (DO), D84.3 (DI)
unnamed: D84.1 (DO), D85.3 (DI)
unnamed: D85.1 (DO), D86.3 (DI)
unnamed: D86.1 (DO), D87.3 (DI)
unnamed: D87.1 (DO), D88.3 (DI)
unnamed: D88.1 (DO), D89.3 (DI)
unnamed: D89.1 (DO), D90.3 (DI)
unnamed: D90.1 (DO), D91.3 (DI)
unnamed: D91.1 (DO), D92.3 (DI)
unnamed: D92.1 (DO), D93.3 (DI)
unnamed: D93.1 (DO), D94.3 (DI)
unnamed: D94.1 (DO), D95.3 (DI)
unnamed: D95.1 (DO), D96.3 (DI)
unnamed: D96.1 (DO), D97.3 (DI)
unnamed: D97.1 (DO), D98.3 (DI)
unnamed: D98.1 (DO), D99.3 (DI)
unnamed: D99.1 (DO), D100.3 (DI)
unnamed: D100.1 (DO), D101.3 (DI)
unnamed: D101.1 (DO), D102.3 (DI)
unnamed: D102.1 (DO), D103.3 (DI)
unnamed: D103.1 (DO), D104.3 (DI)
unnamed: D104.1 (DO), D105.3 (DI)
unnamed: D105.1 (DO), D106.3 (DI)
unnamed: D106.1 (DO), D107.3 (DI)
unnamed: D107.1 (DO), D108.3 (DI)
unnamed: D108.1 (DO), D109.3 (DI)
unnamed: D109.1 (DO), D110.3 (DI)
unnamed: D110.1 (DO), D111.3 (DI)
unnamed: D111.1 (DO), D112.3 (DI)
unnamed: D112.1 (DO), D113.3 (DI)
unnamed: D113.1 (DO), D114.3 (DI)
unnamed: D114.1 (DO), D115.3 (DI)
unnamed: D115.1 (DO), D116.3 (DI)
unnamed: D116.1 (DO), D117.3 (DI)
unnamed: D117.1 (DO), D118.3 (DI)
unnamed: D118.1 (DO), D119.3 (DI)
unnamed: D119.1 (DO), D120.3 (DI)
unnamed: D120.1 (DO), D121.3 (DI)
unnamed: D121.1 (DO), D122.3 (DI)
unnamed: D122.1 (DO), D123.3 (DI)
unnamed: D123.1 (DO), D124.3 (DI)
unnamed: D124.1 (DO), D125.3 (DI)
unnamed: D125.1 (DO), D126.3 (DI)
unnamed: D126.1 (DO), D127.3 (DI)
unnamed: D127.1 (DO), D128.3 (DI)
unnamed: D128.1 (DO), J5.2

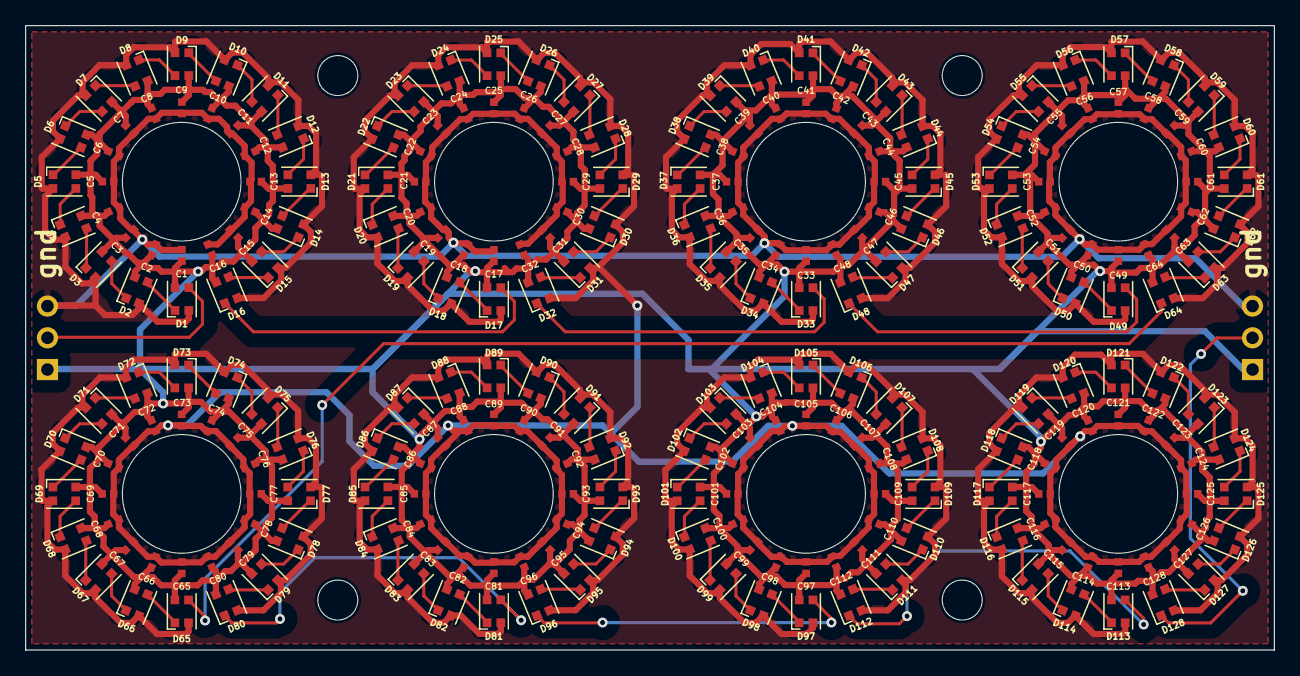
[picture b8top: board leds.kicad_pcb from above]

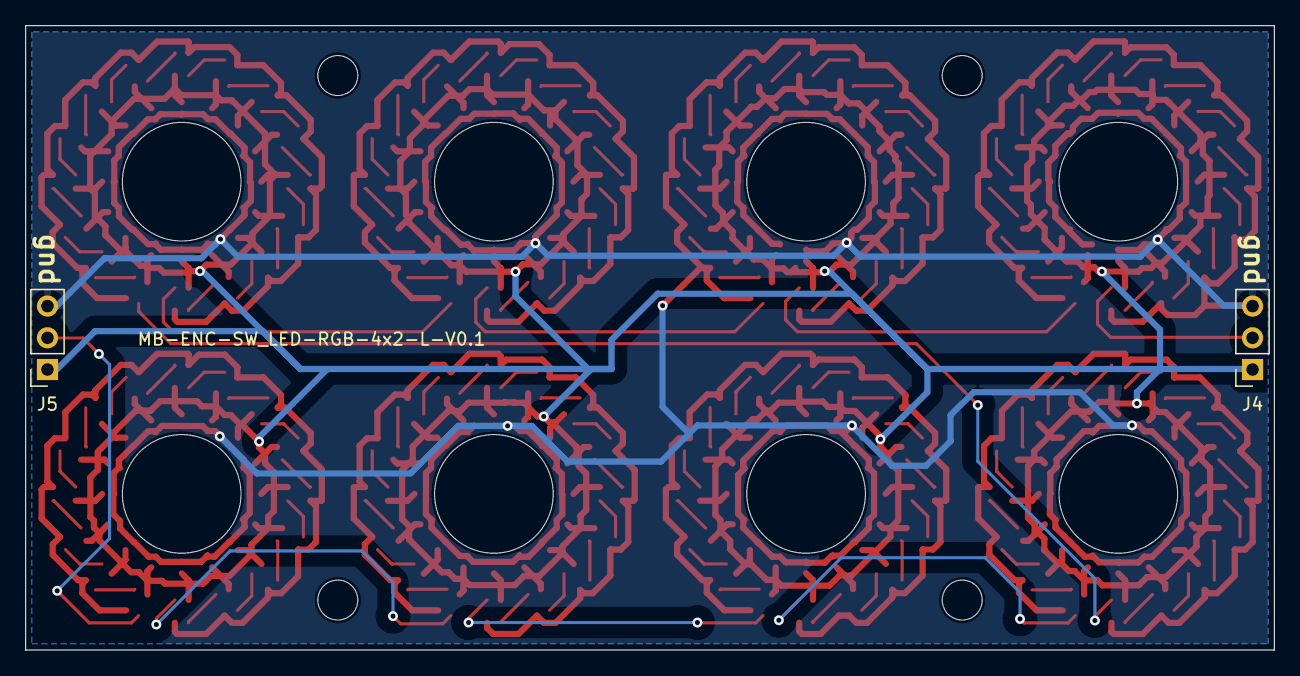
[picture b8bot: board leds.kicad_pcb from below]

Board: 2 copper layers, 100.0 x 50.0 mm, 270 parts (2 on the bottom side), 131 nets.

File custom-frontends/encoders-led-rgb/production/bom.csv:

Designator,Footprint,Quantity,Value,LCSC Part #
"C1, C10, C100, C101, C102, C103, C104, C105, C106, C107, C108, C109, C11, C110, C111, C112, C113, C114, C115, C116, C117, C118, C119, C12, C120, C121, C122, C123, C124, C125, C126, C127, C128, C13, C14, C15, C16, C17, C18, C19, C2, C20, C21, C22, C23, C24, C25, C26, C27, C28, C29, C3, C30, C31, C32, C33, C34, C35, C36, C37, C38, C39, C4, C40, C41, C42, C43, C44, C45, C46, C47, C48, C49, C5, C50, C51, C52, C53, C54, C55, C56, C57, C58, C59, C6, C60, C61, C62, C63, C64, C65, C66, C67, C68, C69, C7, C70, C71, C72, C73, C74, C75, C76, C77, C78, C79, C8, C80, C81, C82, C83, C84, C85, C86, C87, C88, C89, C9, C90, C91, C92, C93, C94, C95, C96, C97, C98, C99",CAPC1005X55N,128,100nf,C1525
"D1, D10, D100, D101, D102, D103, D104, D105, D106, D107, D108, D109, D11, D110, D111, D112, D113, D114, D115, D116, D117, D118, D119, D12, D120, D121, D122, D123, D124, D125, D126, D127, D128, D13, D14, D15, D16, D17, D18, D19, D2, D20, D21, D22, D23, D24, D25, D26, D27, D28, D29, D3, D30, D31, D32, D33, D34, D35, D36, D37, D38, D39, D4, D40, D41, D42, D43, D44, D45, D46, D47, D48, D49, D5, D50, D51, D52, D53, D54, D55, D56, D57, D58, D59, D6, D60, D61, D62, D63, D64, D65, D66, D67, D68, D69, D7, D70, D71, D72, D73, D74, D75, D76, D77, D78, D79, D8, D80, D81, D82, D83, D84, D85, D86, D87, D88, D89, D9, D90, D91, D92, D93, D94, D95, D96, D97, D98, D99",LED_WS2812B-2020_PLCC4_2.0x2.0mm,128,WS2812-2020,C2976072
"H1, H13, H14, H15, H16, H17, H18, H19, H2, H20, H3, H4",MountingHole_3.2mm_M3,12,MountingHole,
"H10, H11, H12, H5, H6, H7, H8, H9",Hole_9.5mm,8,MountingHole,
"J11, J12, J13",IDC-Header_2x05_P2.54mm_Vertical_ksr_dIN,3,sin_in,
"J14, J15, J34, J35",PinHeader_1x03_P2.54mm_Vertical,4,Conn_01x06_Pin,
"J20, J21, J22, J23",PinSocket_1x06_P2.54mm_Vertical,4,Conn_01x06_Socket,
"J24, J25, J4, J5",PinSocket_1x03_P2.54mm_Vertical,4,Conn_01x06_Socket,
"J30, J31, J32, J33",PinHeader_1x06_P2.54mm_Vertical,4,Conn_01x06_Pin,
"J44, J45",IDC-Header_2x05_P2.54mm_Vertical,2,IDC-Header_2x05_P2.54mm_Vertical,
"SW1, SW2, SW3, SW4, SW5, SW6, SW7, SW8",PEC164120FS0012,8,PEC16-4XXXF-SXXXX,
